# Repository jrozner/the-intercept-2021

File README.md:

# The Intercept 2021

## Building

The code is built against `639e7ad494d93fc82159f9fe854041bc43a96d5f` of the esp-idf. Depending on when you're building it maybe safe to build against whatever the current release is but code for, I think, the ir challenges made it in that were built master and weren't compatible with 4.2 anymore.

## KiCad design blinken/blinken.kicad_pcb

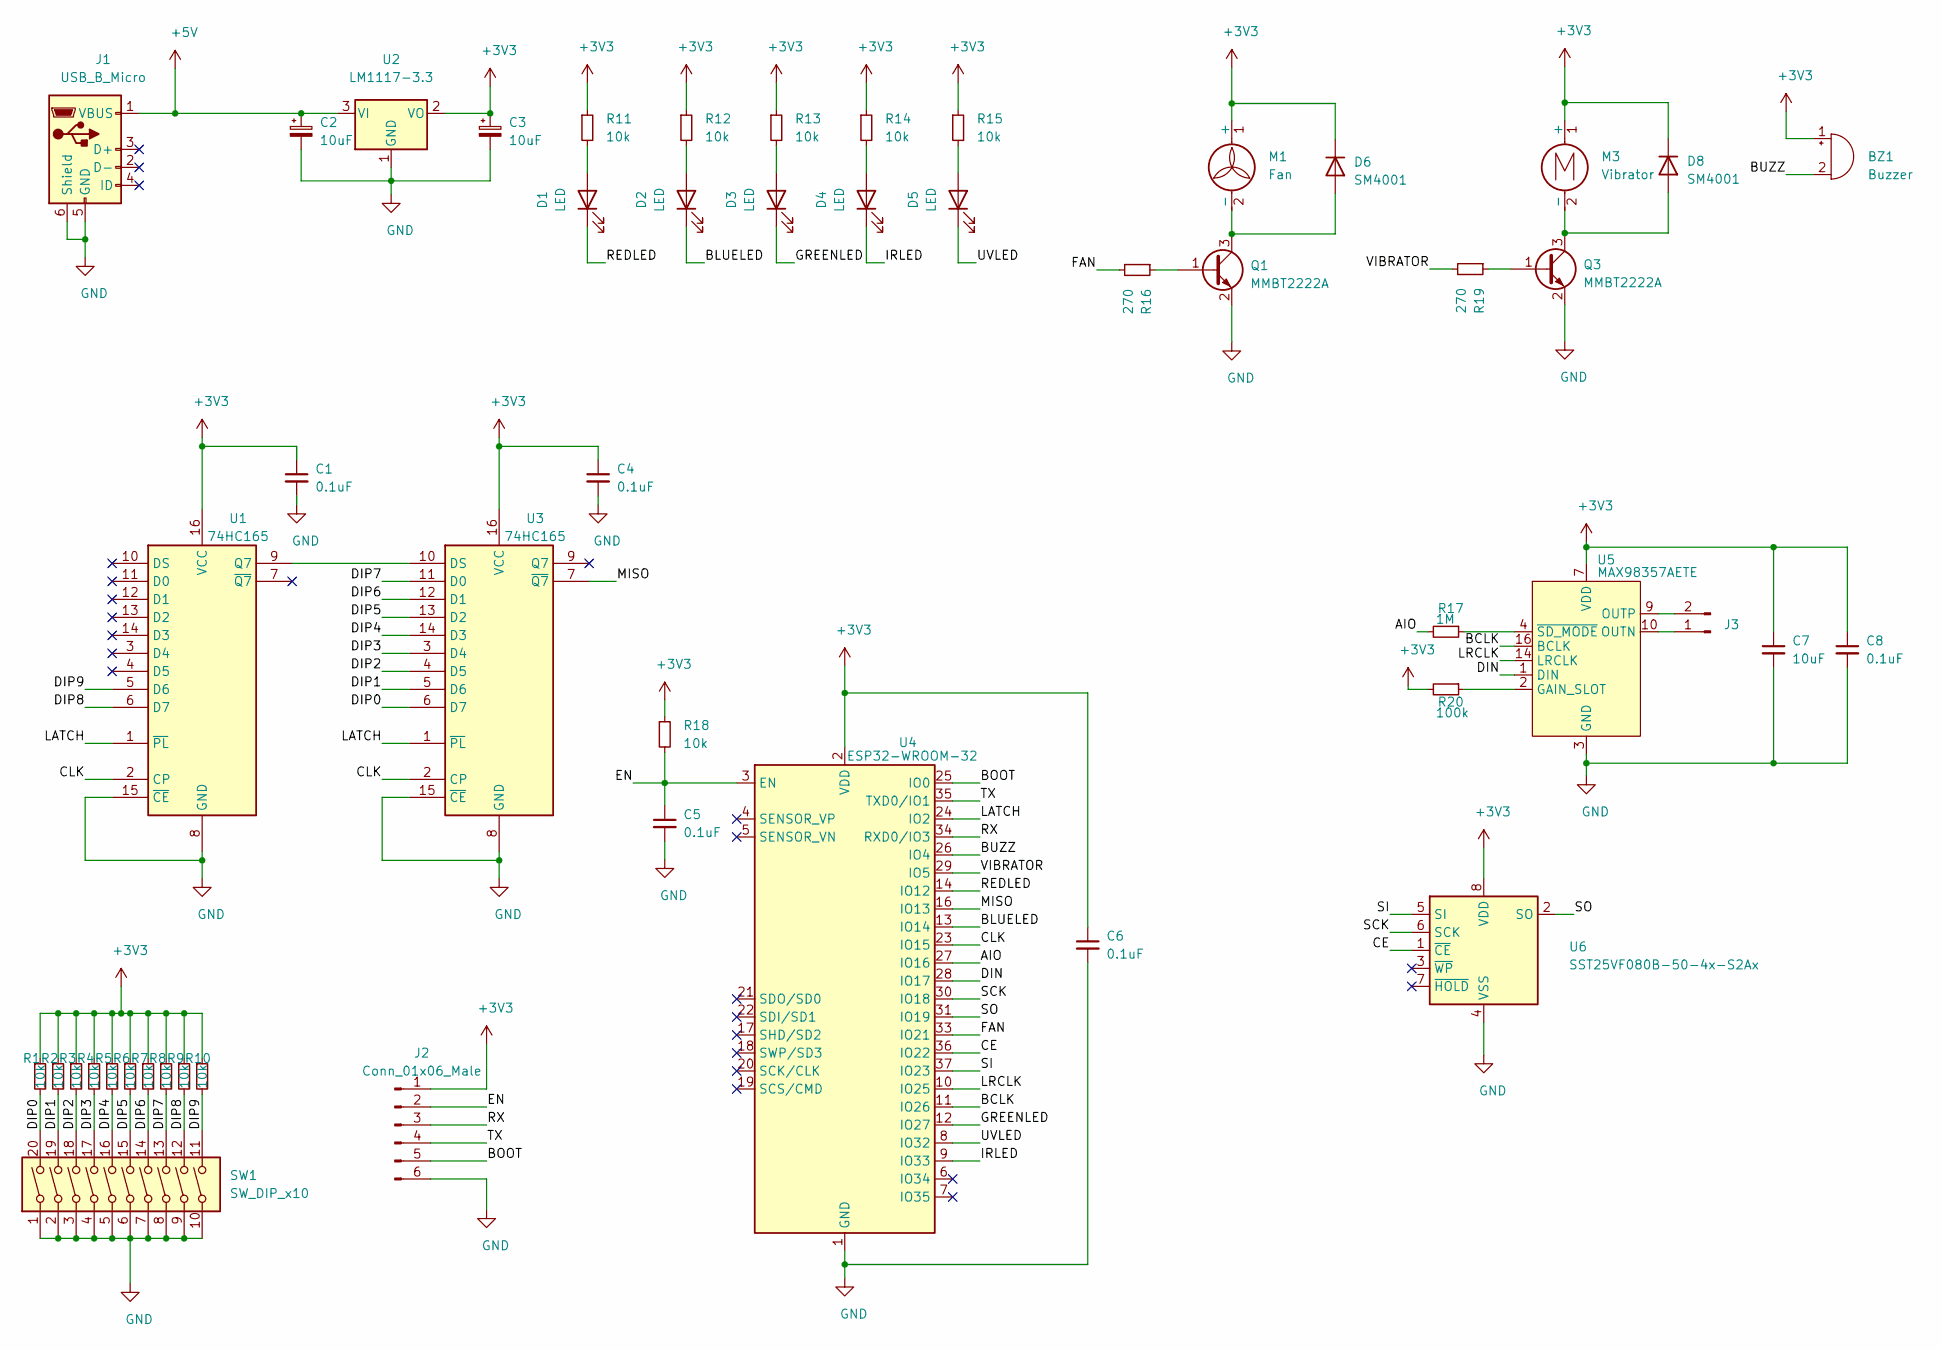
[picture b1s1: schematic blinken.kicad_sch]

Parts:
BZ1: Buzzer; XDCR_CPT-1203-78-SMT-TR
C1, C4, C5, C6, C8: 0.1uF; C_0603_1608Metric
C2, C3, C7: 10uF; C_0603_1608Metric
D1, D2, D3, D4, D5: LED; LED_0603_1608Metric
D6, D8: SM4001; D_SOD-123F
J1: USB_B_Micro; USB_Micro-B_Amphenol_10103594-0001LF_Horizontal
J2: Conn_01x06_Male; programming-pins
J3: Conn_01x02_Male; pads1x2
M1: Fan; pads1x2
M3: Vibrator; pads1x2
Q1, Q3: MMBT2222A; SOT-23
R1, R2, R3, R4, R5, R6, R7, R8, R9, R10, R11, R12, R13, R14, R15, R18: 10k; R_0603_1608Metric
R16, R19: 270; R_0603_1608Metric
R17: 1M; R_0603_1608Metric
R20: 100k; R_0603_1608Metric
SW1: SW_DIP_x10; 10dip
U1, U3: 74HC165; SO-16_3.9x9.9mm_P1.27mm
U2: LM1117-3.3; SOT-223-3_TabPin2
U4: ESP32-WROOM-32
U5: MAX98357AETE; TQFN-16-1EP_3x3mm_P0.5mm_EP1.23x1.23mm
U6: SST25VF080B-50-4x-S2Ax; SOIC-8_3.9x4.9mm_P1.27mm

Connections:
+3V3: BZ1.1 (-), C1.1, C3.1, C4.1, C6.1, C7.1, C8.1, D6.1 (K), D8.1 (K), J2.1, M1.1 (+), M3.1 (+), R1.1, R2.1, R3.1, R4.1, R5.1, R6.1, R7.1, R8.1, R9.1, R10.1, R11.1, R12.1, R13.1, R14.1, R15.1, R18.1, R20.2, U1.16 (VCC), U2.2 (VO), U3.16 (VCC), U4.2 (VDD), U5.7 (VDD), U5.8 (VDD), U6.8 (VDD)
+5V: C2.1, J1.1 (VBUS), U2.3 (VI)
/AIO: R17.2, U4.27 (IO16)
/BCLK: U4.11 (IO26), U5.16 (BCLK)
/BLUELED: D2.1 (K), U4.13 (IO14)
/BOOT: J2.5, U4.25 (IO0)
/BUZZ: BZ1.2 (+), U4.26 (IO4)
/CE: U4.36 (IO22), U6.1 (~CE)
/CLK: U1.2 (CP), U3.2 (CP), U4.23 (IO15)
/DIN: U4.28 (IO17), U5.1 (DIN)
/DIP0: R1.2, SW1.20, U3.6 (D7)
/DIP1: R2.2, SW1.19, U3.5 (D6)
/DIP2: R3.2, SW1.18, U3.4 (D5)
/DIP3: R4.2, SW1.17, U3.3 (D4)
/DIP4: R5.2, SW1.16, U3.14 (D3)
/DIP5: R6.2, SW1.15, U3.13 (D2)
/DIP6: R7.2, SW1.14, U3.12 (D1)
/DIP7: R8.2, SW1.13, U3.11 (D0)
/DIP8: R9.2, SW1.12, U1.6 (D7)
/DIP9: R10.2, SW1.11, U1.5 (D6)
/EN: C5.1, J2.2, R18.2, U4.3 (EN)
/FAN: R16.2, U4.33 (IO21)
/GREENLED: D3.1 (K), U4.12 (IO27)
/IRLED: D4.1 (K), U4.9 (IO33)
/LATCH: U1.1 (~PL), U3.1 (~PL), U4.24 (IO2)
/LRCLK: U4.10 (IO25), U5.14 (LRCLK)
/MISO: U3.7 (~Q7), U4.16 (IO13)
/REDLED: D1.1 (K), U4.14 (IO12)
/RX: J2.3, U4.34 (RXD0/IO3)
/SCK: U4.30 (IO18), U6.6 (SCK)
/SI: U4.37 (IO23), U6.5 (SI)
/SO: U4.31 (IO19), U6.2 (SO)
/TX: J2.4, U4.35 (TXD0/IO1)
/UVLED: D5.1 (K), U4.8 (IO32)
/VIBRATOR: R19.2, U4.29 (IO5)
GND: C1.2, C2.2, C3.2, C4.2, C5.2, C6.2, C7.2, C8.2, J1.5 (GND), J1.6 (Shield), J2.6, Q1.2 (E), Q3.2 (E), SW1.1, SW1.2, SW1.3, SW1.4, SW1.5, SW1.6, SW1.7, SW1.8, SW1.9, SW1.10, U1.8 (GND), U1.15 (~CE), U2.1 (GND), U3.8 (GND), U3.15 (~CE), U4.1 (GND), U4.15 (GND), U4.38 (GND), U4.39 (GND), U5.3 (GND), U5.11 (GND), U5.15 (GND), U6.4 (VSS)
unnamed: D1.2 (A), R11.2
unnamed: D2.2 (A), R12.2
unnamed: D3.2 (A), R13.2
unnamed: D4.2 (A), R14.2
unnamed: D5.2 (A), R15.2
unnamed: D6.2 (A), M1.2 (-), Q1.3 (C)
unnamed: D8.2 (A), M3.2 (-), Q3.3 (C)
unnamed: J3.1, U5.10 (OUTN)
unnamed: J3.2, U5.9 (OUTP)
unnamed: Q1.1 (B), R16.1
unnamed: Q3.1 (B), R19.1
unnamed: R17.1, U5.4 (~SD_MODE)
unnamed: R20.1, U5.2 (GAIN_SLOT)
unnamed: U1.9 (Q7), U3.10 (DS)

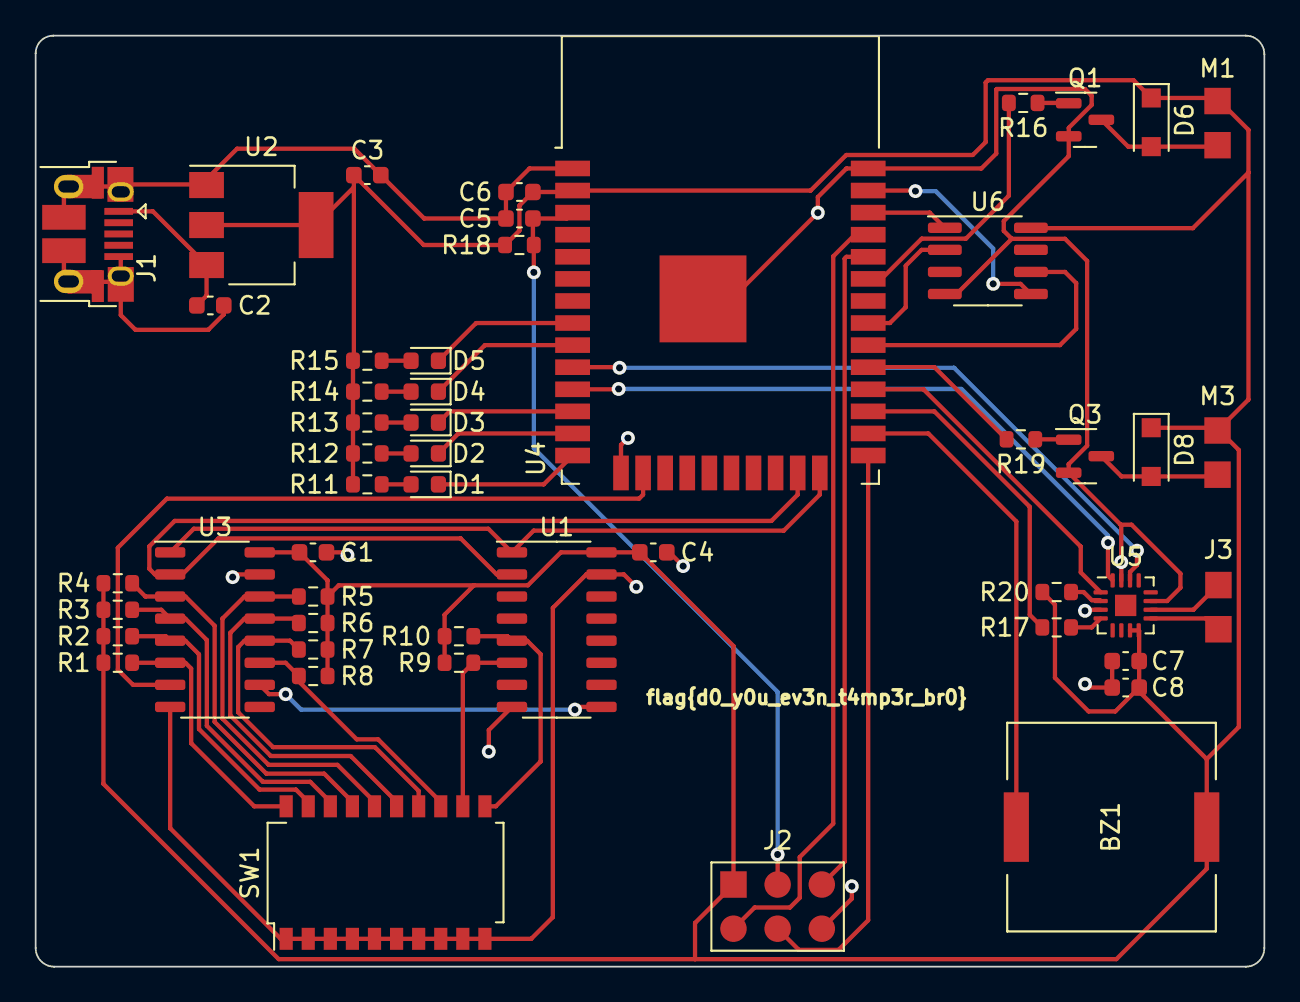
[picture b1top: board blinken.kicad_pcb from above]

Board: 2 copper layers, 70.7 x 53.5 mm, 50 parts (0 on the bottom side), 50 nets.

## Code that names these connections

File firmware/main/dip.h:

#ifndef THEINTERCEPT_DIP_H
#define THEINTERCEPT_DIP_H

#define DIP1 (1 << 7)
#define DIP2 (1 << 6)
#define DIP3 (1 << 5)
#define DIP4 (1 << 4)
#define DIP5 (1 << 3)
#define DIP6 (1 << 2)
#define DIP7 (1 << 1)
#define DIP8 (1 << 0)
#define DIP9 (1 << 15)
#define DIP10 (1 << 14)

// DIP SETTINGS 0-1023

#define DIP_CODE(code) (((code & 0b11) << 14) | (code >> 2))

#define CODE_UNLOCK                      (DIP_CODE(951))  // 1110110111
#define CODE_BUZZER_MORSE                (DIP_CODE(420))  // 0110100100
#define CODE_BUZZER_ADVANCED_MORSE       (DIP_CODE(360))  // 0101101000
#define CODE_INFRASOUND                  (DIP_CODE(831))  // 1100111111
#define CODE_NUMBERS                     (DIP_CODE(44))   // 0000101100
#define CODE_NUMBERS2                    (DIP_CODE(357))  // 0101100101
#define CODE_DTMF                        (DIP_CODE(555))  // 1000101011
#define CODE_DTMF2                       (DIP_CODE(213))  // 0011010101
#define CODE_TAP                         (DIP_CODE(124))  // 0001111100

#define CODE_WIFI_AP                     (DIP_CODE(445))  // 0110111101
#define CODE_WIFI_AP2                    (DIP_CODE(770))  // 1100000010
#define CODE_WIFI_MAC                    (DIP_CODE(85))   // 0001010101
#define CODE_WIFI_PROBE                  (DIP_CODE(10))   // 0000001010
#define CODE_WIFI_APCRACK                (DIP_CODE(626))  // 1001110010

#define CODE_HEAT                        (DIP_CODE(640))  // 1010000000
#define CODE_FAN1                        (DIP_CODE(232))  // 0011101000
#define CODE_BAUDOT                      (DIP_CODE(55))   // 0000110111
#define CODE_PSK31                       (DIP_CODE(871))  // 1101100111
#define CODE_SSTV                        (DIP_CODE(136))  // 0010001000
#define CODE_LED_IMG_BINARY              (DIP_CODE(164))  // 0010100100
#define CODE_LED_IMG_REDVAR              (DIP_CODE(864))  // 1101100000
#define CODE_LED_IMG_RGB                 (DIP_CODE(540))  // 1000011100
#define CODE_LED_IMG_RGBVAR              (DIP_CODE(735))  // 1011011111
#define CODE_LED_UV                      (DIP_CODE(1001)) // 1111101001
#define CODE_LED_IR                      (DIP_CODE(1023)) // 1111111111
#define CODE_LED_IR2                     (DIP_CODE(666))  // 1010011010
#define CODE_LED_BRAILLE                 (DIP_CODE(333))  // 0101001101
#define CODE_LED_POV                     (DIP_CODE(42))   // 0000101010

#define CODE_SPI                         (DIP_CODE(432))  // 0110110000

uint16_t read_state(spi_device_handle_t);
void load_registers(spi_transaction_t *t);


#endif //THEINTERCEPT_DIP_H

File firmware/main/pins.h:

#ifndef THEINTERCEPT_PINS_H
#define THEINTERCEPT_PINS_H

#include "driver/gpio.h"

// IS2 audio DAC
#define I2S_BCK_PIN (GPIO_NUM_26)
#define I2S_WS_PIN (GPIO_NUM_25)
#define I2S_DO_PIN (GPIO_NUM_17)
#define I2S_DI_PIN (-1)
#define I2S_AIO_PIN (GPIO_NUM_16)

// LEDs
#define RED_LED_PIN (GPIO_NUM_12)
#define BLUE_LED_PIN (GPIO_NUM_14)
#define GREEN_LED_PIN (GPIO_NUM_27)
#define IR_LED_PIN (GPIO_NUM_33)
#define UV_LED_PIN (GPIO_NUM_32)

// Misc peripherals
#define VIBRATOR_PIN (GPIO_NUM_5)
#define BUZZER_PIN (GPIO_NUM_4)
#define FAN_PIN (GPIO_NUM_21)

// DIP
#define LATCH_PIN (GPIO_NUM_2)
#define DIP_MISO (GPIO_NUM_13)
#define DIP_SCLK (GPIO_NUM_15)

// Flash
#define FLASH_MISO (GPIO_NUM_19)
#define FLASH_MOSI (GPIO_NUM_23)
#define FLASH_SCK (GPIO_NUM_18)
#define FLASH_CE (GPIO_NUM_22)

#endif //THEINTERCEPT_PINS_H

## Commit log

2021-04-08 Add prototype hardware
2021-04-15 Begin firmware cleanup
2021-04-18 First pass at morse with buzzer
    If possible we might want to use C++ lambdas or C blocks to pass
    anonymous functions to the morse function so that we don't have to
    implement the switch statement for each peripheral that is going to use
    it.
2021-04-18 Play startup animation
2021-04-18 More cleanup
2021-04-20 Implement lock logic
    This allows teams to get access to the hardware but not start on
    challenges until they unlock the device which requires guessing a 2^10
    code.
2021-04-23 added DIP_CODE for sane dip code representation
2021-04-23 fixed morse, added buzzer advanced morse challenge
2021-04-23 added swing to buzzer advanced morse to defeat decoders online
2021-04-23 Testing audio code
2021-04-23 added subsonic test
2021-04-23 Final revision of pcb
2021-05-01 adding dip rsvps
2021-05-01 Added LED challenge basics, fixed audio on boot
2021-05-02 blue led chal done, fixed dip typo
2021-05-03 rgb binary and uart challenge added
2021-05-03 Added variable LED challenges, moved LED challenge data to not-DRAM
2021-05-04 added UV challenge, some code refactor. fixed jk's bullshit
2021-05-04 Remove warnings
2021-05-04 added infrasound challenge
2021-05-04 Added numbers station base
2021-05-04 added number station data
2021-05-04 IR test code
2021-05-04 Fixed IR challenge #1 for NEC encoding
2021-05-05 Add test firmware
2021-05-05 IR challenge 2 done
2021-05-05 Added POV LED challenge
2021-05-05 added numbers station 1
2021-05-06 shuffled dip settings
2021-05-06 minor change to numbers station
2021-05-06 Added new dip settings
2021-05-06 added dtmf challenge
2021-05-06 Baudot done
2021-05-06 added tap code challenge
2021-05-06 Moved bullshit around so double includes stop happening
2021-05-06 Added Baudot, PSK31, SSTV and moved audio data around
2021-05-08 Added fan and CPU challenge, may update later
2021-05-08 AP1 and AP2 done
2021-05-08 added dtmf #2
2021-05-08 Fixed jk's bullshit, added wifi stubs
2021-05-08 added numbers station 2
2021-05-08 Added final wifi challenges
2021-05-09 Beta testing apcrack
2021-05-09 Simplified APCRACK
2021-05-09 Removed BLE wah wah wah
2021-05-09 Add eeprom read challenge
2021-05-09 Add README
2021-05-09 Remove bad merge data
2021-05-10 fixed led challenges by using duty_resolution=8
2021-05-10 FINAL REV - NVS disabled because of horse shit
